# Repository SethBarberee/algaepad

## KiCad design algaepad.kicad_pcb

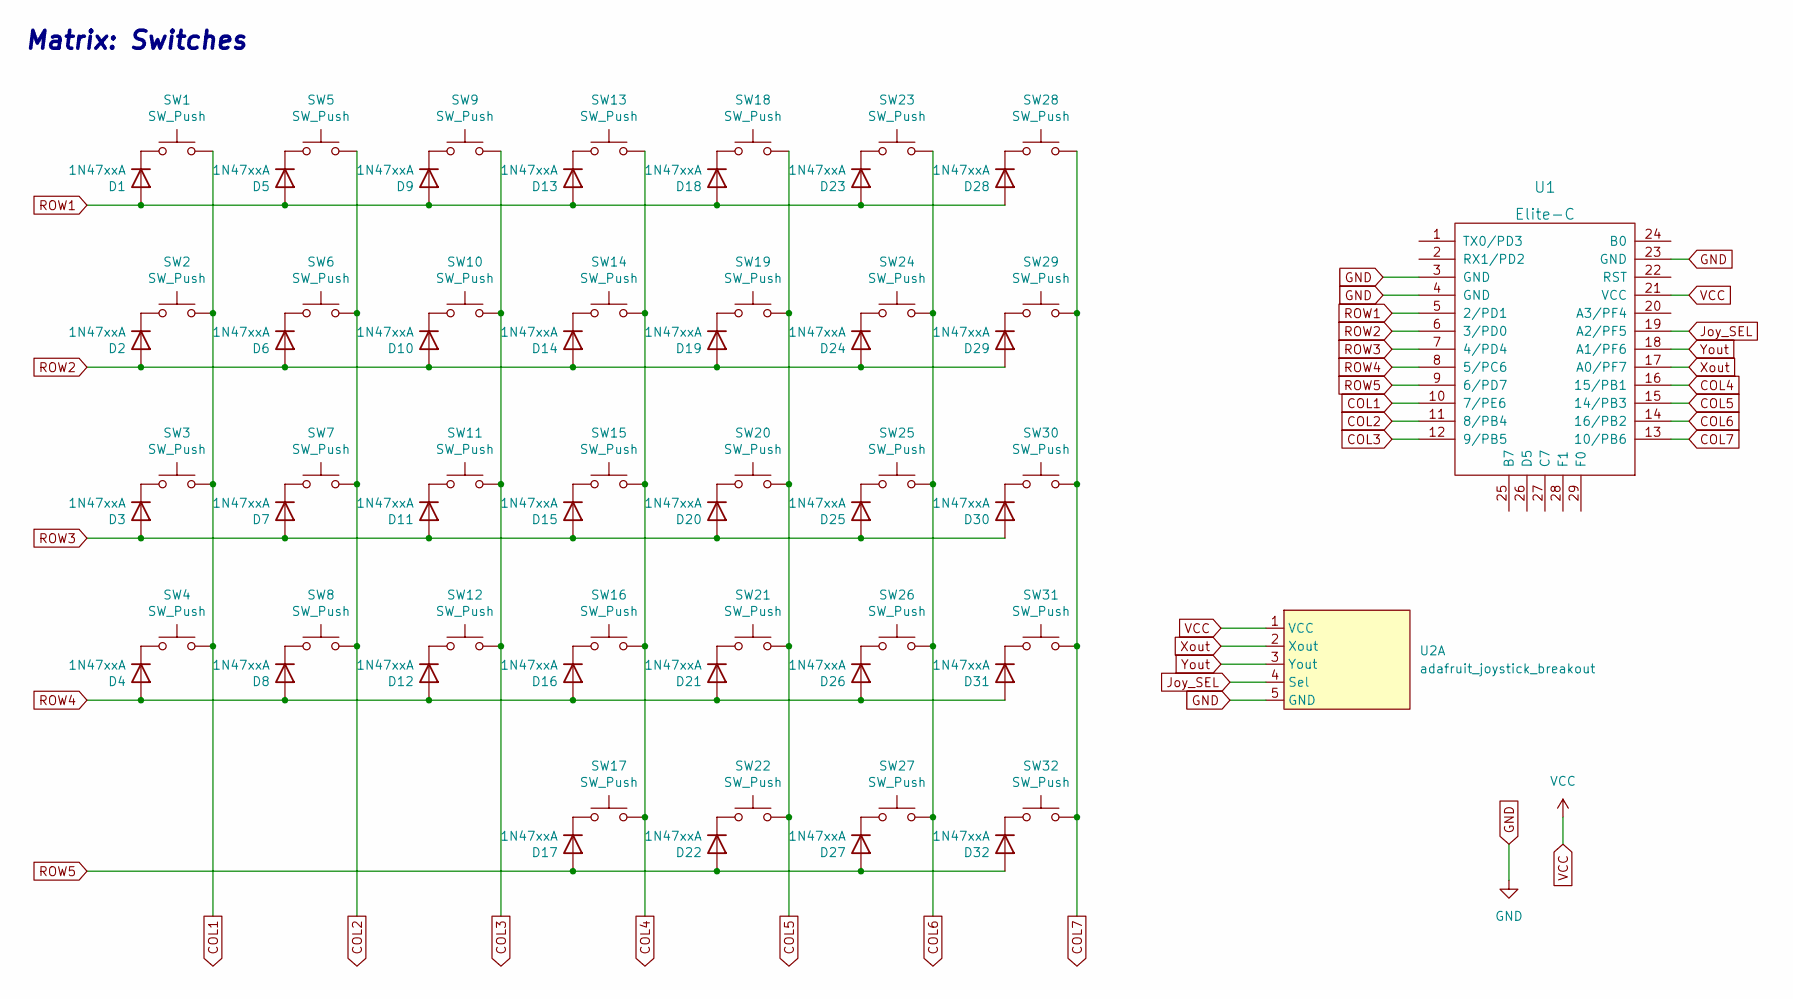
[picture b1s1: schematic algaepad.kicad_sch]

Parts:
D1, D2, D3, D4, D5, D6, D7, D8, D9, D10, D11, D12, D13, D14, D15, D16, D17, D18, D19, D20, D21, D22, D23, D24, D25, D26, D27, D28, D29, D30, D31, D32: 1N47xxA; D_DO-41_SOD81_P10.16mm_Horizontal
SW1, SW2, SW3, SW4, SW5, SW6, SW7, SW8, SW9, SW10, SW11, SW12, SW13, SW14, SW15, SW16, SW17, SW18, SW19, SW20, SW21, SW22, SW23, SW24, SW25, SW26, SW27, SW28, SW29, SW30, SW31, SW32: SW_Push; MX-1U-Hotswap
U1: Elite-C
U2: adafruit_joystick_breakout

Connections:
COL1: SW1.2, SW2.2, SW3.2, SW4.2, U1.10 (7/PE6)
COL2: SW5.2, SW6.2, SW7.2, SW8.2, U1.11 (8/PB4)
COL3: SW9.2, SW10.2, SW11.2, SW12.2, U1.12 (9/PB5)
COL4: SW13.2, SW14.2, SW15.2, SW16.2, SW17.2, U1.16 (15/PB1)
COL5: SW18.2, SW19.2, SW20.2, SW21.2, SW22.2, U1.15 (14/PB3)
COL6: SW23.2, SW24.2, SW25.2, SW26.2, SW27.2, U1.14 (16/PB2)
COL7: SW28.2, SW29.2, SW30.2, SW31.2, SW32.2, U1.13 (10/PB6)
GND: U1.3 (GND), U1.4 (GND), U1.23 (GND), U2.5 (GND)
Joy_SEL: U1.19 (A2/PF5), U2.4 (Sel)
unnamed: D1.1 (K), SW1.1
unnamed: D2.1 (K), SW2.1
unnamed: D3.1 (K), SW3.1
unnamed: D4.1 (K), SW4.1
unnamed: D5.1 (K), SW5.1
unnamed: D6.1 (K), SW6.1
unnamed: D7.1 (K), SW7.1
unnamed: D8.1 (K), SW8.1
unnamed: D9.1 (K), SW9.1
unnamed: D10.1 (K), SW10.1
unnamed: D11.1 (K), SW11.1
unnamed: D12.1 (K), SW12.1
unnamed: D13.1 (K), SW13.1
unnamed: D14.1 (K), SW14.1
unnamed: D15.1 (K), SW15.1
unnamed: D16.1 (K), SW16.1
unnamed: D17.1 (K), SW17.1
unnamed: D18.1 (K), SW18.1
unnamed: D19.1 (K), SW19.1
unnamed: D20.1 (K), SW20.1
unnamed: D21.1 (K), SW21.1
unnamed: D22.1 (K), SW22.1
unnamed: D23.1 (K), SW23.1
unnamed: D24.1 (K), SW24.1
unnamed: D25.1 (K), SW25.1
unnamed: D26.1 (K), SW26.1
unnamed: D27.1 (K), SW27.1
unnamed: D28.1 (K), SW28.1
unnamed: D29.1 (K), SW29.1
unnamed: D30.1 (K), SW30.1
unnamed: D31.1 (K), SW31.1
unnamed: D32.1 (K), SW32.1
ROW1: D1.2 (A), D5.2 (A), D9.2 (A), D13.2 (A), D18.2 (A), D23.2 (A), D28.2 (A), U1.5 (2/PD1)
ROW2: D2.2 (A), D6.2 (A), D10.2 (A), D14.2 (A), D19.2 (A), D24.2 (A), D29.2 (A), U1.6 (3/PD0)
ROW3: D3.2 (A), D7.2 (A), D11.2 (A), D15.2 (A), D20.2 (A), D25.2 (A), D30.2 (A), U1.7 (4/PD4)
ROW4: D4.2 (A), D8.2 (A), D12.2 (A), D16.2 (A), D21.2 (A), D26.2 (A), D31.2 (A), U1.8 (5/PC6)
ROW5: D17.2 (A), D22.2 (A), D27.2 (A), D32.2 (A), U1.9 (6/PD7)
VCC: U1.21 (VCC), U2.1 (VCC)
Xout: U1.17 (A0/PF7), U2.2 (Xout)
Yout: U1.18 (A1/PF6), U2.3 (Yout)

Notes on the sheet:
Matrix: Switches

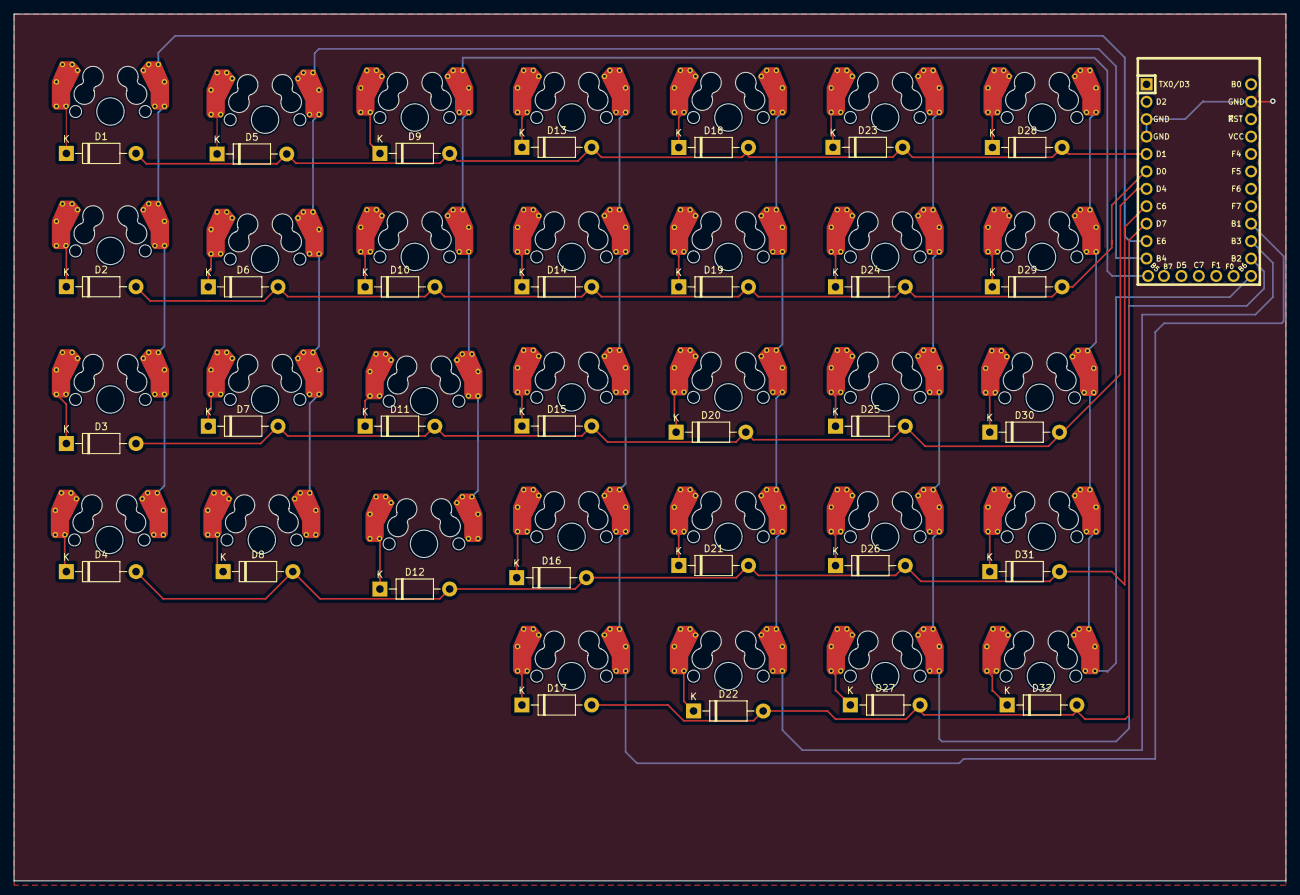
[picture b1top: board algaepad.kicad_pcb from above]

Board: 2 copper layers, 185.4 x 126.4 mm, 65 parts (0 on the bottom side), 45 nets.

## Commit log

2023-03-05 starting draft of algaepad
2023-03-06 fix up footprints so basic layout can be started
2023-03-06 add adafruit joystick symbol in a custom algaepad library
2023-03-06 start work in layout
2023-03-07 first attempt at complete pcb layout
2023-03-09 switch to SMT diode
